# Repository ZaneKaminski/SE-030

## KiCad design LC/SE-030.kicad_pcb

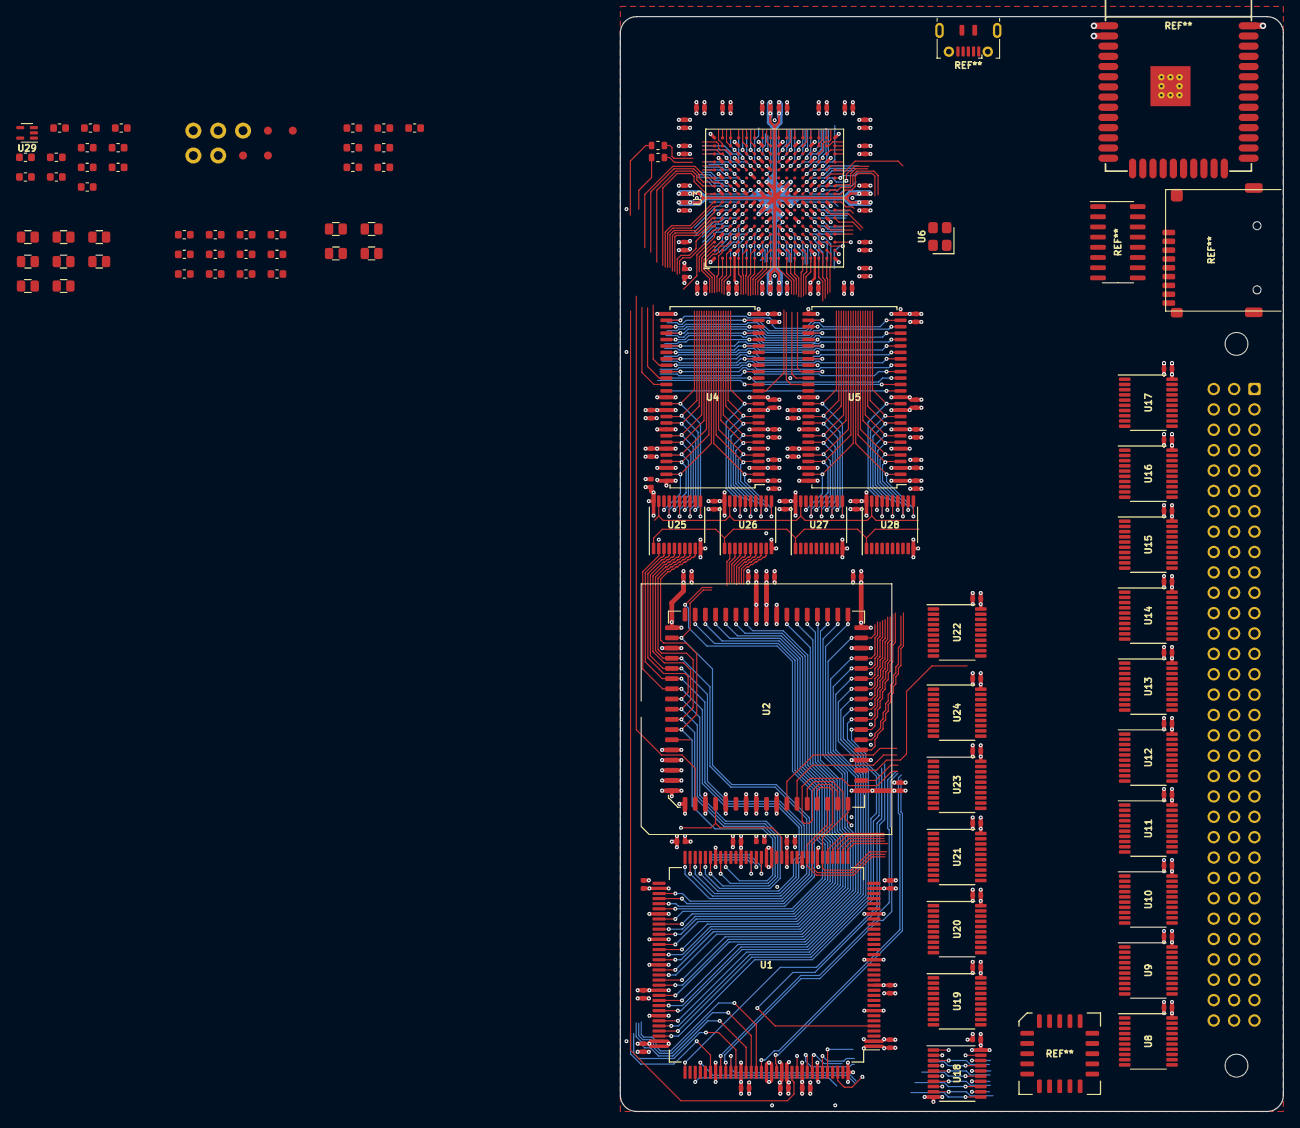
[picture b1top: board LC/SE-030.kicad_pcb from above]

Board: 4 copper layers, 82.7 x 136.5 mm, 80 parts (0 on the bottom side), 175 nets.

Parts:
C4, C5, C6, C7, C8, C9, C10, C11, C12, C13, C14, C15: 10u; C_0805
C16, C17, C18, C19, C20, C21, C22, C23, C24, C25, C26, C27, C28, C29, C30, C31, C32, C33, C34, C35, C36, C37, C38, C39, C40, C41, C42, C43, C44, C45, C46: 2u2; C_0603
FID1, FID2, FID3, FID4: Fiducial
H1, H2, H3, H4, H5: PasteHole_1.1mm_PTH
U1: MC68030FE; PQFP-132_24x24mm_P0.635mm_MC68030
U2: MC68882FN; PLCC-68_SMDSocket
U3: XC6SLX9-FTG256; BGA-256_17.0x17.0mm_Layout16x16_P1.0mm_Ball0.5mm_Pad0.4mm_N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
U4, U5: W9825G6KH-6; TSOP-II-54_22.2x10.16mm_P0.8mm
U6: 50M; Crystal_SMD_3225-4Pin_3.2x2.5mm
U8, U9, U10, U11, U12, U22: 74AHCT573PW; TSSOP-20_4.4x6.5mm_P0.65mm
U13, U23, U24: 74LVC244APW; TSSOP-20_4.4x6.5mm_P0.65mm
U14, U15, U16, U17, U25, U26, U27, U28: 74AHC245APW; TSSOP-20_4.4x6.5mm_P0.65mm
U18, U19, U20, U21: 74LVC244; TSSOP-20_4.4x6.5mm_P0.65mm
U29: 74LVC1G125GW; SOT-353

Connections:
+1V2: U3.G7, U3.G9, U3.H8, U3.H10, U3.J7, U3.J9, U3.K8, U3.K10
+3V3: C16.1, C17.1, C18.1, C19.1, C20.1, C21.1, C22.1, C23.1, C24.1, C25.1, C26.1, C27.1, C28.1, C29.1, C30.1, C31.1, C32.1, C33.1, C34.1, C35.1, C36.1, C37.1, C38.1, C39.1, C40.1, C41.1, C42.1, C43.1, C44.1, C45.1, C46.1, U3.B4, U3.B9, U3.B13, U3.D2, U3.D7, U3.D10, U3.D15, U3.E5, U3.F8, U3.F11, U3.G4, U3.G10, U3.G13, U3.H6, U3.J2, U3.J10, U3.J15, U3.K4, U3.K13, U3.L6, U3.L9, U3.N2, U3.N7, U3.N10, U3.N15, U3.R4, U3.R8, U3.R13, U4.1, U4.3, U4.9, U4.14, U4.27, U4.43, U4.49, U5.1, U5.3, U5.9, U5.14, U5.27, U5.43, U5.49, U13.20, U14.20, U15.20, U16.20, U17.20, U18.20, U19.20, U20.20, U21.20, U22.11, U22.20, U23.20, U24.20, U25.20, U26.20, U27.20, U28.20, U29.5
+5V: C4.1, C5.1, C12.1, C13.1, C14.1, C15.1, U1.4, U1.8, U1.17, U1.18, U1.20, U1.30, U1.49, U1.63, U1.65, U1.71, U1.72, U1.85, U1.105, U1.115, U1.116, U1.128, U2.10, U2.16, U2.17, U2.18, U2.26, U2.27, U2.43, U2.52, U2.53, U2.61, U8.11, U8.20, U9.20, U10.20, U11.20, U12.6, U12.20
+12V: C8.1, C9.1
-5V: C6.1, C7.1
-12V: C10.1, C11.1
/CPUBuf/A~OE~: U18.1, U18.19, U19.1, U19.19, U20.1, U20.19, U21.1, U21.19, U24.1, U24.19
/CPUBuf/CPU_D0: U1.75, U2.3, U25.9
/CPUBuf/CPU_D1: U1.76, U2.2, U25.8
/CPUBuf/CPU_D2: U1.78, U2.1, U25.6
/CPUBuf/CPU_D3: U1.79, U2.68, U25.4
/CPUBuf/CPU_D4: U1.80, U2.67, U25.2
/CPUBuf/CPU_D5: U1.81, U2.66, U25.3
/CPUBuf/CPU_D6: U1.82, U2.65, U25.5
/CPUBuf/CPU_D7: U1.83, U2.64, U25.7
/CPUBuf/CPU_D8: U1.86, U2.62, U26.3
/CPUBuf/CPU_D9: U1.87, U2.60, U26.2
/CPUBuf/CPU_D10: U1.88, U2.59, U26.4
/CPUBuf/CPU_D11: U1.89, U2.58, U26.5
/CPUBuf/CPU_D12: U1.91, U2.57, U26.6
/CPUBuf/CPU_D13: U1.92, U2.56, U26.7
/CPUBuf/CPU_D14: U1.93, U2.55, U26.8
/CPUBuf/CPU_D15: U1.94, U2.54, U26.9
/CPUBuf/CPU_D16: U1.96, U2.50, U27.2
/CPUBuf/CPU_D17: U1.97, U2.49, U27.3
/CPUBuf/CPU_D18: U1.98, U2.48, U27.4
/CPUBuf/CPU_D19: U1.99, U2.47, U27.5
/CPUBuf/CPU_D20: U1.101, U2.46, U27.6
/CPUBuf/CPU_D21: U1.102, U2.45, U27.7
/CPUBuf/CPU_D22: U1.103, U2.44, U27.9
/CPUBuf/CPU_D23: U1.104, U2.42, U27.8
/CPUBuf/CPU_D24: U1.106, U2.40, U28.2
/CPUBuf/CPU_D25: U1.107, U2.39, U28.3
/CPUBuf/CPU_D26: U1.108, U2.38, U28.4
/CPUBuf/CPU_D27: U1.109, U2.37, U28.5
/CPUBuf/CPU_D28: U1.111, U2.36, U28.6
/CPUBuf/CPU_D29: U1.112, U2.35, U28.7
/CPUBuf/CPU_D30: U1.113, U2.34, U28.8
/CPUBuf/CPU_D31: U1.114, U2.33, U28.9
/CPUBuf/CPU_FC0: U1.12, U24.17
/CPUBuf/CPU_FC1: U1.10, U24.8
/CPUBuf/CPU_FC2: U1.9, U24.6
/CPUBuf/CPU_R~W~: U1.117, U2.28, U24.4
/CPUBuf/CPU_SIZ0: U1.120, U23.15
/CPUBuf/CPU_SIZ1: U1.119, U23.13
/CPUBuf/CPU_~AS~: U1.125, U2.21, U23.2
/CPUBuf/CPU_~CBREQ~: U1.126, U23.4
/CPUBuf/CPU_~CIOUT~: U1.15, U23.17
/CPUBuf/CPU_~DSACK~0: U1.3, U2.31, U22.18
/CPUBuf/CPU_~DSACK~1: U1.132, U2.32, U22.19
/CPUBuf/CPU_~DS~: U1.124, U2.20, U23.6
/CPUBuf/CPU_~ECS~: U1.118, U23.8
/CPUBuf/CPU_~RMC~: U1.13, U24.2
/CPUBuf/FSB_A4: U12.5, U18.3
/CPUBuf/FSB_A5: U12.4, U18.5
/CPUBuf/FSB_A6: U12.3, U18.7
/CPUBuf/FSB_A7: U12.2, U18.9
/CPUBuf/FSB_A8: U11.9, U19.12
/CPUBuf/FSB_A9: U11.8, U19.14
/CPUBuf/FSB_A10: U11.7, U19.16
/CPUBuf/FSB_A11: U11.6, U19.18
/CPUBuf/FSB_A12: U11.5, U19.3
/CPUBuf/FSB_A13: U11.4, U19.5
/CPUBuf/FSB_A14: U11.3, U19.7
/CPUBuf/FSB_A15: U11.2, U19.9
/CPUBuf/FSB_A16: U10.9, U20.12
/CPUBuf/FSB_A17: U10.8, U20.14
/CPUBuf/FSB_A18: U10.7, U20.16
/CPUBuf/FSB_A19: U10.6, U20.18
/CPUBuf/FSB_A20: U10.5, U20.3
/CPUBuf/FSB_A21: U10.4, U20.5
/CPUBuf/FSB_A22: U10.3, U20.7
/CPUBuf/FSB_A23: U10.2, U20.9
/CPUBuf/FSB_A24: U9.9, U21.12
/CPUBuf/FSB_A25: U9.8, U21.14
/CPUBuf/FSB_A26: U9.7, U21.16
/CPUBuf/FSB_A27: U9.6, U21.18
/CPUBuf/FSB_A30: U9.5, U21.7
/CPUBuf/FSB_A31: U9.4, U21.9
/CPUBuf/FSB_FC0: U12.9, U24.3
/CPUBuf/FSB_FC1: U12.8, U24.18
/CPUBuf/FSB_FC2: U12.7, U24.16
/CPUBuf/FSB_R~W~: U9.3, U24.14
/Control/CPU_DDIR: U25.1, U26.1, U27.1, U28.1
/Control/CPU_D~OE~: U25.19, U26.19, U27.19, U28.19
/Control/RAM_~CAS~: U4.17, U5.17
/Control/RAM_~CS~: U4.19, U5.19
/Control/RAM_~RAS~: U4.18, U5.18
/Control/RAM_~WE~: U4.16, U5.16
/MC68k/A0: U1.21, U18.2
/MC68k/A1: U1.22, U2.25, U18.4
/MC68k/A2: U1.59, U2.24, U18.6
/MC68k/A3: U1.58, U2.23, U18.8
/MC68k/A4: U1.56, U2.22, U18.17
/MC68k/A5: U1.55, U18.15
/MC68k/A6: U1.54, U18.13
/MC68k/A7: U1.53, U18.11
/MC68k/A8: U1.52, U19.2
/MC68k/A9: U1.51, U19.4
/MC68k/A10: U1.48, U19.6
/MC68k/A11: U1.47, U19.8
/MC68k/A12: U1.46, U19.17
/MC68k/A13: U1.45, U19.15
/MC68k/A14: U1.43, U19.13
/MC68k/A15: U1.42, U19.11
/MC68k/A16: U1.41, U20.2
/MC68k/A17: U1.40, U20.4
/MC68k/A18: U1.39, U20.6
/MC68k/A19: U1.38, U20.8
/MC68k/A20: U1.37, U20.17
/MC68k/A21: U1.36, U20.15
/MC68k/A22: U1.34, U20.13
/MC68k/A23: U1.33, U20.11
/MC68k/A24: U1.32, U21.2
/MC68k/A25: U1.31, U21.4
/MC68k/A26: U1.29, U21.6
/MC68k/A27: U1.28, U21.8
/MC68k/A28: U1.27, U21.17
/MC68k/A29: U1.26, U21.15
/MC68k/A30: U1.24, U21.13
/MC68k/A31: U1.23, U21.11
/PDSBuf/ADoutLE: U9.11, U10.11, U11.11, U12.11
/PDSBuf/A~OE~: U8.1, U9.1, U10.1, U11.1, U12.1
/PDSBuf/DDIR: U14.1, U15.1, U16.1, U17.1
/PDSBuf/D~OE~: U14.19, U15.19, U16.19, U17.19
/PDSBuf/IOB_~RESET~: U1.64, U2.13, U13.2
/RAM/BA0: U4.20, U5.20
/RAM/BA1: U4.21, U5.21
/RAM/CKE: U4.37, U5.37
/RAM/D0: U4.2, U25.11
/RAM/D1: U4.4, U25.12
/RAM/D2: U4.5, U25.14
/RAM/D3: U4.7, U25.16
/RAM/D4: U4.8, U25.18
/RAM/D5: U4.10, U25.17
/RAM/D6: U4.11, U25.15
/RAM/D7: U4.13, U25.13
/RAM/D8: U4.42, U26.17
/RAM/D9: U4.44, U26.18
/RAM/D10: U4.45, U26.16
/RAM/D11: U4.47, U26.15
/RAM/D12: U4.48, U26.14
/RAM/D13: U4.50, U26.13
/RAM/D14: U4.51, U26.12
/RAM/D15: U4.53, U26.11
/RAM/D16: U5.2, U27.18
/RAM/D17: U5.4, U27.17
/RAM/D18: U5.5, U27.16
/RAM/D19: U5.7, U27.15
/RAM/D20: U5.8, U27.14
/RAM/D21: U5.10, U27.13
/RAM/D22: U5.11, U27.11
/RAM/D23: U5.13, U27.12
/RAM/D24: U5.42, U28.18
/RAM/D25: U5.44, U28.17
/RAM/D26: U5.45, U28.16
/RAM/D27: U5.47, U28.15
/RAM/D28: U5.48, U28.14
/RAM/D29: U5.50, U28.13
/RAM/D30: U5.51, U28.12
/RAM/D31: U5.53, U28.11
/RAM/RA0: U4.23, U5.23
/RAM/RA1: U4.24, U5.24
/RAM/RA2: U4.25, U5.25
/RAM/RA3: U4.26, U5.26
/RAM/RA4: U4.29, U5.29
/RAM/RA5: U4.30, U5.30
/RAM/RA6: U4.31, U5.31
/RAM/RA7: U4.32, U5.32
/RAM/RA8: U4.33, U5.33
/RAM/RA9: U4.34, U5.34
/RAM/RA10: U4.22, U5.22
/RAM/RA11: U4.35, U5.35
/RAM/RA12: U4.36, U5.36
GND: C4.2, C5.2, C6.2, C7.2, C8.2, C9.2, C10.2, C11.2, C12.2, C13.2, C14.2, C15.2, C16.2, C17.2, C18.2, C19.2, C20.2, C21.2, C22.2, C23.2, C24.2, C25.2, C26.2, C27.2, C28.2, C29.2, C30.2, C31.2, C32.2, C33.2, C34.2, C35.2, C36.2, C37.2, C38.2, C39.2, C40.2, C41.2, C42.2, C43.2, C44.2, C45.2, C46.2, H1.1, H2.1, H3.1, H4.1, H5.1, U1.1, U1.2, U1.5, U1.7, U1.11, U1.19, U1.25, U1.35, U1.44, U1.57, U1.60, U1.66, U1.67, U1.77, U1.90, U1.95, U1.100, U1.110, U1.123, U2.5, U2.6, U2.7, U2.8, U2.9, U2.12, U2.14, U2.19, U2.30, U2.41, U2.51, U2.63, U3.A1, U3.A16, U3.B7, U3.B11, U3.D4, U3.D13, U3.E9, U3.G2, U3.G8, U3.G15, U3.H7, U3.H9, U3.H12, U3.J5, U3.J8, U3.K7, U3.K9, U3.L2, U3.L15, U3.M8, U3.N13, U3.P3, U3.R6, U3.R10, U3.T1, U3.T16, U4.6, U4.12, U4.28, U4.41, U4.46, U4.52, U4.54, U5.6, U5.12, U5.28, U5.41, U5.46, U5.52, U5.54, U8.10, U9.2, U9.10, U10.10, U11.10, U12.10, U13.1, U13.10, U13.11, U13.13, U13.19, U14.10, U15.10, U16.10, U17.10, U18.10, U19.10, U20.10, U21.10, U22.10, U23.1, U23.10, U23.11, U23.19, U24.10, U24.11, U24.13, U24.15, U25.10, U26.10, U27.10, U28.10, U29.2, U29.3

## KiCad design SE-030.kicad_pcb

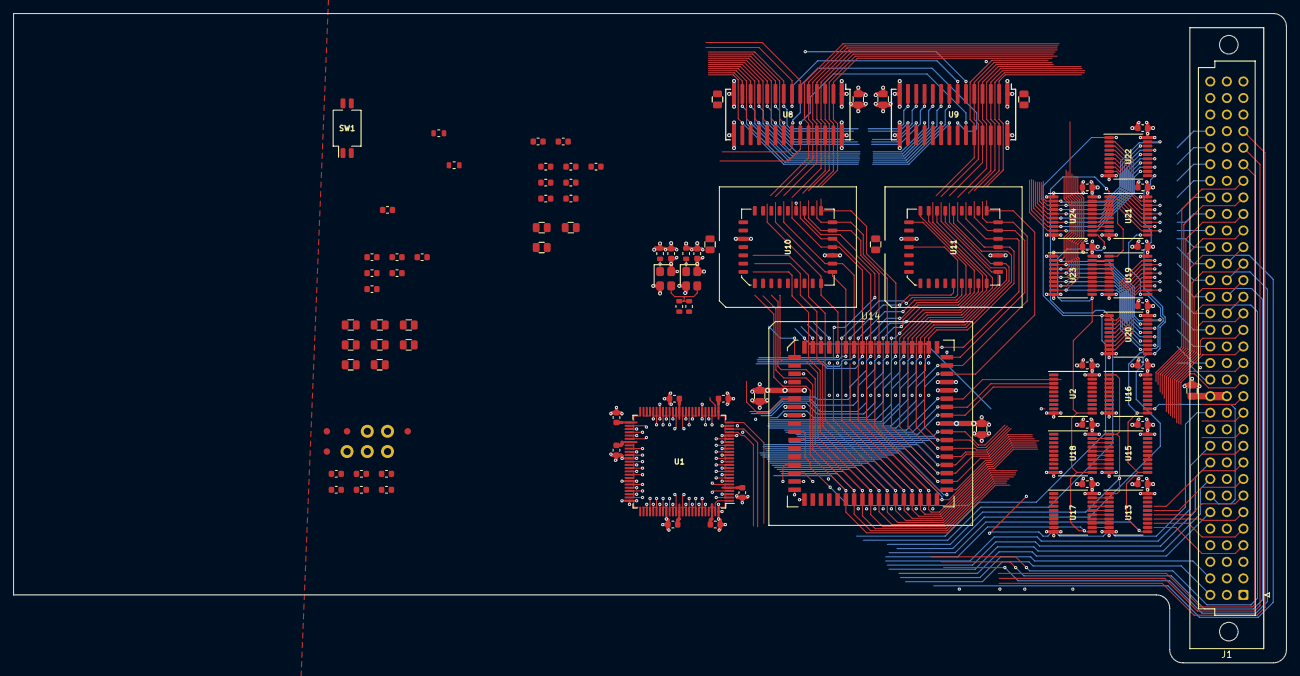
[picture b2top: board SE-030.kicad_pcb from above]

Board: 4 copper layers, 195.2 x 99.6 mm, 100 parts (0 on the bottom side), 178 nets.

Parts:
C1, C1#2, C1#3, C1#4, C1#5, C1#6, C1#7, C1#8, C1#9, C2, C3, C4, C18, C19, C20, C21, C22, C23, C24, C25: 10u; C_0805
C5, C6, C7, C10, C11, C12, C13, C14, C14#2, C14#3, C14#4, C14#5, C14#6, C14#7, C14#8, C14#9, C14#10, C14#11, C14#12, C14#13, C15, C16, C17, C26, C27, C28, C29, C30, C31, C32, C33, C34, C35, C36, C37, C38, C39, C40, C41, C41#2, C42, C43, C44: 2u2; C_0603
FID1, FID2, FID3, FID4: Fiducial
H1, H2, H3, H4, H5: PasteHole_1.1mm_PTH
J1: MacSEPDS; DIN41612_R_3x32_Male_Vertical_THT
R1, R2, R6, R12: 22; R_0603
R10, R11: 10k; R_0603
SW1: OSCSEL; SW_DIP_SPSTx02_Slide_DSHP02TS_P1.27mm
U1: XC95144XL-TQ100; TQFP-100_14x14mm_P0.5mm
U2, U13, U15, U16, U17, U18, U19, U20, U21, U22, U23, U24: 74AHCT573; TSSOP-20_4.4x6.5mm_P0.65mm
U4: 20M; Crystal_SMD_3225-4Pin_3.2x2.5mm
U5: 25M; Crystal_SMD_3225-4Pin_3.2x2.5mm
U8, U9: KM48C2100; SOJ-28_300mil
U10, U11: 39SF040; PLCC-32_SMDSocket
U14: MC68HC000FN20; PLCC-68_SMD-Socket

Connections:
+3V3: C5.1, C6.1, C7.1, C26.1, C27.1, C28.1, C29.1, C30.1, C31.1, C32.1, C33.1, C34.1, C35.1, C36.1, C37.1, C38.1, C39.1, C40.1, C41.1, C41#2.1, C42.1, C43.1, C44.1, R12.1, U1.5, U1.26, U1.38, U1.51, U1.57, U1.88, U1.98, U4.4, U5.4, U10.32, U11.32
+5V: C1.1, C1#2.1, C1#3.1, C1#4.1, C1#5.1, C1#6.1, C1#7.1, C1#8.1, C1#9.1, C2.1, C3.1, C4.1, C10.1, C11.1, C12.1, C13.1, C14.1, C14#2.1, C14#3.1, C14#4.1, C14#5.1, C14#6.1, C14#7.1, C14#8.1, C14#9.1, C14#10.1, C14#11.1, C14#12.1, C14#13.1, C15.1, C16.1, C17.1, C18.1, C19.1, J1.B13, J1.B14, J1.B15, J1.B16, J1.B17, J1.C4, J1.C13, U2.20, U13.20, U14.12, U14.13, U14.14, U14.52, U15.20, U16.20, U17.20, U18.20, U19.20, U20.20, U21.20, U22.20, U23.20, U24.20
+12V: C22.1, C23.1
-5V: C20.1, C21.1
-12V: C24.1, C25.1
/Buf/ADoutLE0: U1.4, U13.11, U15.11, U16.11, U19.11, U21.11
/Buf/ADoutLE1: U1.3, U2.11, U17.11, U18.11, U23.11, U24.11
/Buf/AccD0: U8.2, U10.13, U14.5, U20.12, U23.9
/Buf/AccD1: U8.3, U10.14, U14.4, U20.13, U23.8
/Buf/AccD2: U8.4, U10.15, U14.3, U20.14, U23.7
/Buf/AccD3: U8.5, U10.17, U14.2, U20.15, U23.6
/Buf/AccD4: U8.24, U10.18, U14.1, U20.16, U23.5
/Buf/AccD5: U8.25, U10.19, U14.68, U20.17, U23.4
/Buf/AccD6: U8.26, U10.20, U14.67, U20.18, U23.3
/Buf/AccD7: U8.27, U10.21, U14.66, U20.19, U23.2
/Buf/AccD8: U9.2, U11.13, U14.65, U22.12, U24.9
/Buf/AccD9: U9.3, U11.14, U14.64, U22.13, U24.8
/Buf/AccD10: U9.4, U11.15, U14.63, U22.14, U24.7
/Buf/AccD11: U9.5, U11.17, U14.62, U22.15, U24.6
/Buf/AccD12: U9.24, U11.18, U14.61, U22.16, U24.5
/Buf/AccD13: U9.25, U11.19, U14.60, U22.17, U24.4
/Buf/AccD14: U9.26, U11.20, U14.59, U22.18, U24.3
/Buf/AccD15: U9.27, U11.21, U14.58, U22.19, U24.2
/Buf/Aout~OE~: U1.2, U13.1, U15.1, U16.1
/Buf/DinLE: U1.8, U20.11, U22.11
/Buf/Din~OE~: U1.7, U20.1, U22.1
/Buf/Dout~OE~: U1.6, U19.1, U21.1
/Buf/Mac~R~W: J1.C7, U16.12
/Control/A1: U1.77, U10.12, U11.12, U14.32, U17.9
/Control/A2: U1.76, U10.11, U11.11, U14.33, U17.8
/Control/A3: U1.74, U10.10, U11.10, U14.34, U17.7
/Control/A4: U1.49, U10.9, U11.9, U14.35, U17.6
/Control/A5: U1.46, U10.8, U11.8, U14.36, U17.5
/Control/A6: U1.43, U10.7, U11.7, U14.37, U17.4
/Control/A7: U1.42, U10.6, U11.6, U14.38, U17.3
/Control/A8: U1.41, U10.5, U11.5, U14.39, U17.2
/Control/A9: U1.40, U10.27, U11.27, U14.40, U18.9
/Control/A10: U1.39, U10.26, U11.26, U14.41, U18.8
/Control/A11: U1.37, U10.23, U11.23, U14.42, U18.7
/Control/A12: U1.36, U10.25, U11.25, U14.43, U18.6
/Control/A13: U1.35, U10.4, U11.4, U14.44, U18.5
/Control/A14: U1.20, U10.28, U11.28, U14.45, U18.4
/Control/A15: U1.19, U10.29, U11.29, U14.46, U18.3
/Control/A16: U1.18, U10.3, U11.3, U14.47, U18.2
/Control/A17: U1.17, U2.8, U10.2, U11.2, U14.48
/Control/A18: U1.16, U2.7, U10.30, U11.30, U14.49
/Control/A19: U1.15, U2.6, U10.1, U11.1, U14.50
/Control/A20: U1.14, U2.5, U14.51
/Control/A21: U1.13, U2.4, U14.53
/Control/A22: U1.12, U2.3, U14.54
/Control/A23: U1.11, U2.2, U14.55
/Control/AccR~W~: U1.78, U2.9, U14.9
/Control/Acc~AS~: U1.70, U14.6
/Control/Acc~BERR~: U1.72, U14.24
/Control/Acc~DTACK: U1.71, U14.10
/Control/Acc~LDS~: U1.68, U14.8
/Control/Acc~UDS~: U1.67, U14.7
/Control/Acc~VPA~: U1.73, U14.23
/Control/C8M: J1.A28, U1.27
/Control/C16M: J1.A29, U1.23
/Control/FCLK: R2.2, U1.22
/Control/L~WE~: U1.65, U8.6, U10.31
/Control/Mac~AS~: J1.C10, U1.87
/Control/Mac~BERR~: J1.B21, U1.94
/Control/Mac~DTACK~: J1.C6, U1.92
/Control/Mac~LDS~: J1.C8, U1.90
/Control/Mac~UDS~: J1.C9, U1.91
/Control/Mac~VMA~: J1.C2, U1.89
/Control/Mac~VPA~: J1.C1, U1.93
/Control/RA0: U1.81, U8.10, U9.10
/Control/RA1: U1.82, U8.11, U9.11
/Control/RA2: U1.85, U8.12, U9.12
/Control/RA3: U1.86, U8.13, U9.13
/Control/RA4: U1.50, U8.16, U9.16
/Control/RA5: U1.52, U8.17, U9.17
/Control/RA6: U1.53, U8.18, U9.18
/Control/RA7: U1.54, U8.19, U9.19
/Control/RA8: U1.55, U8.20, U9.20
/Control/RA9: U1.56, U8.21, U9.21
/Control/RA10: U1.58, U8.9, U9.9
/Control/RA11: U1.59, U8.8, U9.8
/Control/ROM~CS~: U1.63, U10.22, U11.22
/Control/U~WE~: U1.66, U9.6, U11.31
/Control/~CAS~: U1.61, U8.23, U9.23
/Control/~OE~: U1.64, U8.22, U9.22, U10.24, U11.24
/Control/~RAS~: U1.60, U8.7, U9.7
/Control/~RESET~r: U1.1, U1.99
/MC68k/CLK: R1.2, U14.15
/MC68k/~HALT~: J1.C12, U1.10, U14.19, U14.20
/MC68k/~IPL~0: J1.B18, U14.27
/MC68k/~IPL~1: J1.B19, U14.26
/MC68k/~IPL~2: J1.B20, U14.25
/PDS/A1: J1.A4, U13.12
/PDS/A2: J1.A5, U13.13
/PDS/A3: J1.A6, U13.14
/PDS/A4: J1.A7, U13.15
/PDS/A5: J1.A8, U13.16
/PDS/A6: J1.A9, U13.17
/PDS/A7: J1.A10, U13.18
/PDS/A8: J1.A11, U13.19
/PDS/A9: J1.A12, U15.12
/PDS/A10: J1.A13, U15.13
/PDS/A11: J1.A14, U15.14
/PDS/A12: J1.A15, U15.15
/PDS/A13: J1.A16, U15.16
/PDS/A14: J1.A17, U15.17
/PDS/A15: J1.A18, U15.18
/PDS/A16: J1.A19, U15.19
/PDS/A17: J1.A20, U16.13
/PDS/A18: J1.A21, U16.14
/PDS/A19: J1.A22, U16.15
/PDS/A20: J1.A23, U16.16
/PDS/A21: J1.A24, U16.17
/PDS/A22: J1.A25, U16.18
/PDS/A23: J1.A26, U16.19
/PDS/D0: J1.C14, U19.12, U20.9
/PDS/D1: J1.C15, U19.13, U20.8
/PDS/D2: J1.C16, U19.14, U20.7
/PDS/D3: J1.C17, U19.15, U20.6
/PDS/D4: J1.C18, U19.16, U20.5
/PDS/D5: J1.C19, U19.17, U20.4
/PDS/D6: J1.C20, U19.18, U20.3
/PDS/D7: J1.C21, U19.19, U20.2
/PDS/D8: J1.C22, U21.12, U22.9
/PDS/D9: J1.C23, U21.13, U22.8
/PDS/D10: J1.C24, U21.14, U22.7
/PDS/D11: J1.C25, U21.15, U22.6
/PDS/D12: J1.C26, U21.16, U22.5
/PDS/D13: J1.C27, U21.17, U22.4
/PDS/D14: J1.C28, U21.18, U22.3
/PDS/D15: J1.C29, U21.19, U22.2
/PDS/E: J1.A27, U1.95
GND: C1.2, C1#2.2, C1#3.2, C1#4.2, C1#5.2, C1#6.2, C1#7.2, C1#8.2, C1#9.2, C2.2, C3.2, C4.2, C5.2, C6.2, C7.2, C10.2, C11.2, C12.2, C13.2, C14.2, C14#2.2, C14#3.2, C14#4.2, C14#5.2, C14#6.2, C14#7.2, C14#8.2, C14#9.2, C14#10.2, C14#11.2, C14#12.2, C14#13.2, C15.2, C16.2, C17.2, C18.2, C19.2, C20.2, C21.2, C22.2, C23.2, C24.2, C25.2, C26.2, C27.2, C28.2, C29.2, C30.2, C31.2, C32.2, C33.2, C34.2, C35.2, C36.2, C37.2, C38.2, C39.2, C40.2, C41.2, C41#2.2, C42.2, C43.2, C44.2, H1.1, H2.1, H3.1, H4.1, H5.1, J1.A30, J1.B1, J1.B2, J1.B3, J1.B4, J1.B5, J1.B6, J1.B7, J1.B8, J1.B9, J1.B29, J1.C3, J1.C30, R10.1, R11.1, U1.21, U1.31, U1.44, U1.62, U1.69, U1.75, U1.84, U1.100, U2.1, U2.10, U4.2, U5.2, U8.15, U8.28, U9.15, U9.28, U10.16, U11.16, U13.10, U14.16, U14.17, U14.56, U14.57, U15.10, U16.10, U17.1, U17.10, U18.1, U18.10, U19.10, U20.10, U21.10, U22.10, U23.1, U23.10, U24.1, U24.10
unnamed: R1.1, R2.1, U4.3, U5.3
unnamed: R10.2, SW1.2, U5.1
unnamed: R11.2, SW1.1, U4.1
unnamed: R12.2, SW1.3, SW1.4
unnamed: U13.2, U17.19
unnamed: U13.3, U17.18
unnamed: U13.4, U17.17
unnamed: U13.5, U17.16
unnamed: U13.6, U17.15
unnamed: U13.7, U17.14
unnamed: U13.8, U17.13
unnamed: U13.9, U17.12
unnamed: U15.2, U18.19
unnamed: U15.3, U18.18
unnamed: U15.4, U18.17
unnamed: U15.5, U18.16
unnamed: U15.6, U18.15
unnamed: U15.7, U18.14
unnamed: U15.8, U18.13
unnamed: U15.9, U18.12
unnamed: U2.19, U16.2
unnamed: U2.18, U16.3
unnamed: U2.17, U16.4
unnamed: U2.16, U16.5
unnamed: U2.15, U16.6
unnamed: U2.14, U16.7
unnamed: U2.13, U16.8
unnamed: U2.12, U16.9
unnamed: U19.2, U23.19
unnamed: U19.3, U23.18
unnamed: U19.4, U23.17
unnamed: U19.5, U23.16
unnamed: U19.6, U23.15
unnamed: U19.7, U23.14
unnamed: U19.8, U23.13
unnamed: U19.9, U23.12
unnamed: U21.2, U24.19
unnamed: U21.3, U24.18
unnamed: U21.4, U24.17
unnamed: U21.5, U24.16
unnamed: U21.6, U24.15
unnamed: U21.7, U24.14
unnamed: U21.8, U24.13
unnamed: U21.9, U24.12
VDD: U8.1, U8.14, U9.1, U9.14

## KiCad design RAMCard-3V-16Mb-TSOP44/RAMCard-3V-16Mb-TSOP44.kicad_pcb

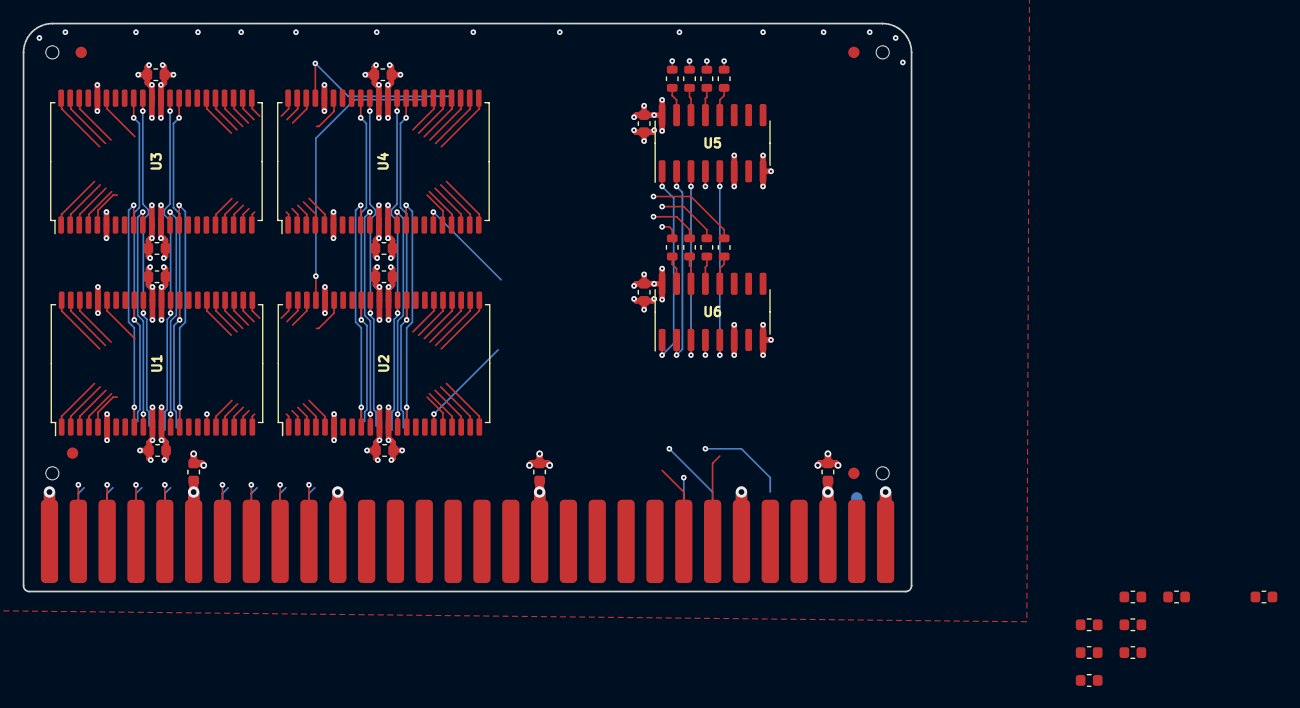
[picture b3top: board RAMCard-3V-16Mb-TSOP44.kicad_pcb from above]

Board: 4 copper layers, 78.2 x 50.0 mm, 44 parts (0 on the bottom side), 60 nets.

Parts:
C1, C2, C3, C4, C5, C6, C7, C8, C9, C9#2, C9#3, C12, C12#2, C13, C14, C15, C17, C18, C20, C21, C22: 2u2; C_0603
FID1, FID2, FID3, FID4: Fiducial
H1, H2, H3, H4: PasteHole_1.152mm_NPTH
J1: RAM; AppleIIeAux_Edge
R1, R2, R3, R4, R5, R6, R7, R8: 47; R_0603
U1, U2, U3, U4: SRAM-1Mx8-TSOP2-44; TSOP-II-44_400mil_P0.8mm
U5, U6: 74LVC138D; SOIC-16_3.9mm

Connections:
+5V: C1.1, C2.1, C3.1, C4.1, C5.1, C6.1, C7.1, C8.1, C9.1, C9#2.1, C9#3.1, C12.1, C12#2.1, C13.1, C14.1, C15.1, C17.1, C18.1, C20.1, C21.1, C22.1, J1.6, J1.18, J1.28, J1.33, J1.43, J1.55, U1.11, U1.33, U1.40, U2.11, U2.33, U2.40, U3.11, U3.33, U3.40, U4.11, U4.33, U4.40, U5.6, U5.16, U6.6, U6.16
/A1: J1.12, U1.5, U2.18, U3.5, U4.18
/A2: J1.49, U1.4, U2.19, U3.4, U4.19
/A3: J1.13, U1.3, U2.20, U3.3, U4.20
/A4: J1.48, U1.2, U2.21, U3.2, U4.21
/A5: J1.14, U1.1, U2.22, U3.1, U4.22
/A6: J1.47, U1.44, U2.23, U3.44, U4.23
/A7: J1.15, U1.43, U2.24, U3.43, U4.24
/A8: J1.46, U1.42, U2.25, U3.42, U4.25
/A9: J1.16, U1.39, U2.26, U3.39, U4.26
/A10: J1.45, U1.28, U2.27, U3.28, U4.27
/A11: J1.17, U1.27, U2.28, U3.27, U4.28
/A12: J1.44, U1.26, U2.39, U3.26, U4.39
/A13: J1.19, U1.25, U2.42, U3.25, U4.42
/A14: J1.42, U1.24, U2.43, U3.24, U4.43
/A15: J1.20, U1.23, U2.44, U3.23, U4.44
/A16: J1.41, U1.22, U2.1, U3.22, U4.1
/A17: J1.21, U1.21, U2.2, U3.21, U4.2
/A18: J1.40, U1.20, U2.3, U3.20, U4.3
/A19: J1.22, U1.19, U2.4, U3.19, U4.4
/A20: J1.39, U1.18, U2.5, U3.18, U4.5
/A21: J1.23, U5.1, U6.1
/A22: J1.38, U5.3, U6.3
/A23: J1.24, U5.5, U6.5
/D0: J1.2, U1.9, U3.9
/D1: J1.59, U1.10, U3.10
/D2: J1.3, U1.13, U3.13
/D3: J1.58, U1.14, U3.14
/D4: J1.4, U1.31, U3.31
/D5: J1.57, U1.32, U3.32
/D6: J1.5, U1.35, U3.35
/D7: J1.56, U1.36, U3.36
/D8: J1.7, U2.9, U4.9
/D9: J1.54, U2.10, U4.10
/D10: J1.8, U2.13, U4.13
/D11: J1.53, U2.14, U4.14
/D12: J1.9, U2.31, U4.31
/D13: J1.52, U2.32, U4.32
/D14: J1.10, U2.35, U4.35
/D15: J1.51, U2.36, U4.36
/L~OE~0: R5.1, U3.41
/L~OE~1: R7.1, U1.41
/L~WE~0: R1.1, U3.17
/L~WE~1: R3.1, U1.17
/R~W~: J1.37, U5.2, U6.2
/U~OE~0: R6.1, U4.41
/U~OE~1: R8.1, U2.41
/U~WE~0: R2.1, U4.17
/U~WE~1: R4.1, U2.17
/~LDS~: J1.35, U5.4
/~UDS~: J1.34, U6.4
GND: C1.2, C2.2, C3.2, C4.2, C5.2, C6.2, C7.2, C8.2, C9.2, C9#2.2, C9#3.2, C12.2, C12#2.2, C13.2, C14.2, C15.2, C17.2, C18.2, C20.2, C21.2, C22.2, J1.1, J1.11, J1.25, J1.30, J1.31, J1.32, J1.36, J1.50, J1.60, U1.6, U1.12, U1.34, U2.6, U2.12, U2.34, U3.6, U3.12, U3.34, U4.6, U4.12, U4.34, U5.8, U6.8
unnamed: R1.2, U5.15
unnamed: R2.2, U6.15
unnamed: R3.2, U5.14
unnamed: R4.2, U6.14
unnamed: R5.2, U5.13
unnamed: R6.2, U6.13
unnamed: R7.2, U5.12
unnamed: R8.2, U6.12

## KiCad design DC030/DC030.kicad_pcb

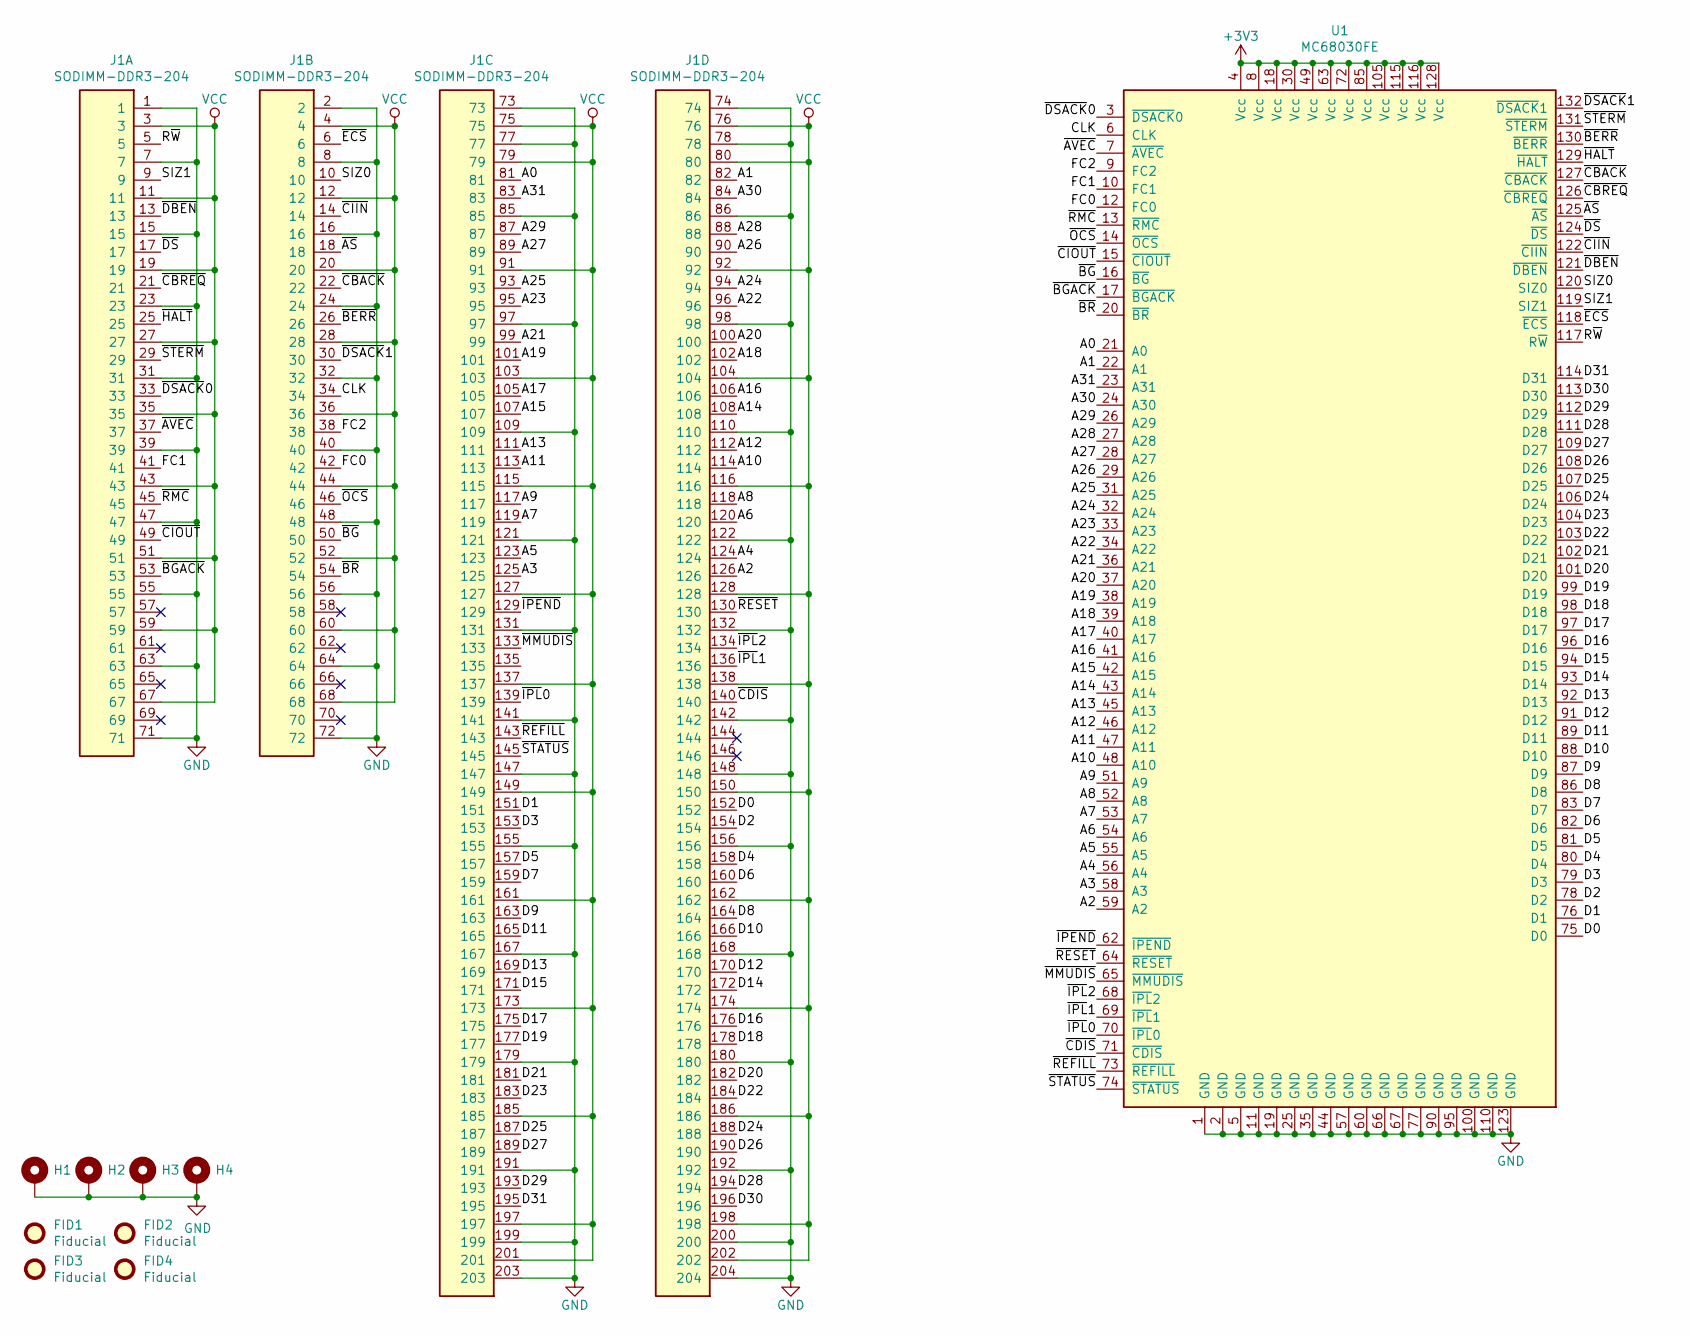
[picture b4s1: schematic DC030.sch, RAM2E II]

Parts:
FID1, FID2, FID3, FID4: Fiducial
H1, H2, H3, H4: PasteHole_1.1mm_PTH
J1: SODIMM-DDR3-204; SODIMM_DDR3_Edge
U1: MC68030FE; Motorola_CQFP-132

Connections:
+3V3: U1.4 (Vcc), U1.8 (Vcc), U1.18 (Vcc), U1.30 (Vcc), U1.49 (Vcc), U1.63 (Vcc), U1.72 (Vcc), U1.85 (Vcc), U1.105 (Vcc), U1.115 (Vcc), U1.116 (Vcc), U1.128 (Vcc)
/A0: J1.81, U1.21 (A0)
/A1: J1.82, U1.22 (A1)
/A2: J1.126, U1.59 (A2)
/A3: J1.125, U1.58 (A3)
/A4: J1.124, U1.56 (A4)
/A5: J1.123, U1.55 (A5)
/A6: J1.120, U1.54 (A6)
/A7: J1.119, U1.53 (A7)
/A8: J1.118, U1.52 (A8)
/A9: J1.117, U1.51 (A9)
/A10: J1.114, U1.48 (A10)
/A11: J1.113, U1.47 (A11)
/A12: J1.112, U1.46 (A12)
/A13: J1.111, U1.45 (A13)
/A14: J1.108, U1.43 (A14)
/A15: J1.107, U1.42 (A15)
/A16: J1.106, U1.41 (A16)
/A17: J1.105, U1.40 (A17)
/A18: J1.102, U1.39 (A18)
/A19: J1.101, U1.38 (A19)
/A20: J1.100, U1.37 (A20)
/A21: J1.99, U1.36 (A21)
/A22: J1.96, U1.34 (A22)
/A23: J1.95, U1.33 (A23)
/A24: J1.94, U1.32 (A24)
/A25: J1.93, U1.31 (A25)
/A26: J1.90, U1.29 (A26)
/A27: J1.89, U1.28 (A27)
/A28: J1.88, U1.27 (A28)
/A29: J1.87, U1.26 (A29)
/A30: J1.84, U1.24 (A30)
/A31: J1.83, U1.23 (A31)
/CLK: J1.34, U1.6 (CLK)
/D0: J1.152, U1.75 (D0)
/D1: J1.151, U1.76 (D1)
/D2: J1.154, U1.78 (D2)
/D3: J1.153, U1.79 (D3)
/D4: J1.158, U1.80 (D4)
/D5: J1.157, U1.81 (D5)
/D6: J1.160, U1.82 (D6)
/D7: J1.159, U1.83 (D7)
/D8: J1.164, U1.86 (D8)
/D9: J1.163, U1.87 (D9)
/D10: J1.166, U1.88 (D10)
/D11: J1.165, U1.89 (D11)
/D12: J1.170, U1.91 (D12)
/D13: J1.169, U1.92 (D13)
/D14: J1.172, U1.93 (D14)
/D15: J1.171, U1.94 (D15)
/D16: J1.176, U1.96 (D16)
/D17: J1.175, U1.97 (D17)
/D18: J1.178, U1.98 (D18)
/D19: J1.177, U1.99 (D19)
/D20: J1.182, U1.101 (D20)
/D21: J1.181, U1.102 (D21)
/D22: J1.184, U1.103 (D22)
/D23: J1.183, U1.104 (D23)
/D24: J1.188, U1.106 (D24)
/D25: J1.187, U1.107 (D25)
/D26: J1.190, U1.108 (D26)
/D27: J1.189, U1.109 (D27)
/D28: J1.194, U1.111 (D28)
/D29: J1.193, U1.112 (D29)
/D30: J1.196, U1.113 (D30)
/D31: J1.195, U1.114 (D31)
/FC0: J1.42, U1.12 (FC0)
/FC1: J1.41, U1.10 (FC1)
/FC2: J1.38, U1.9 (FC2)
/R~W~: J1.5, U1.117 (R~W~)
/SIZ0: J1.10, U1.120 (SIZ0)
/SIZ1: J1.9, U1.119 (SIZ1)
/~AS~: J1.18, U1.125 (~AS~)
/~AVEC~: J1.37, U1.7 (~AVEC~)
/~BERR~: J1.26, U1.130 (~BERR~)
/~BGACK~: J1.53, U1.17 (~BGACK~)
/~BG~: J1.50, U1.16 (~BG~)
/~BR~: J1.54, U1.20 (~BR~)
/~CBACK~: J1.22, U1.127 (~CBACK~)
/~CBREQ~: J1.21, U1.126 (~CBREQ~)
/~CDIS~: J1.140, U1.71 (~CDIS~)
/~CIIN~: J1.14, U1.122 (~CIIN~)
/~CIOUT~: J1.49, U1.15 (~CIOUT~)
/~DBEN~: J1.13, U1.121 (~DBEN~)
/~DSACK~0: J1.33, U1.3 (~DSACK~0)
/~DSACK~1: J1.30, U1.132 (~DSACK~1)
/~DS~: J1.17, U1.124 (~DS~)
/~ECS~: J1.6, U1.118 (~ECS~)
/~HALT~: J1.25, U1.129 (~HALT~)
/~IPEND: J1.129, U1.62 (~IPEND~)
/~IPL~0: J1.139, U1.70 (~IPL~0)
/~IPL~1: J1.136, U1.69 (~IPL~1)
/~IPL~2: J1.134, U1.68 (~IPL~2)
/~MMUDIS~: J1.133, U1.65 (~MMUDIS~)
/~OCS~: J1.46, U1.14 (~OCS~)
/~REFILL~: J1.143, U1.73 (~REFILL~)
/~RESET~: J1.130, U1.64 (~RESET~)
/~RMC~: J1.45, U1.13 (~RMC~)
/~STATUS~: J1.145, U1.74 (~STATUS~)
/~STERM~: J1.29, U1.131 (~STERM~)
GND: H1.1, H2.1, H3.1, H4.1, J1.1, J1.2, J1.7, J1.8, J1.15, J1.16, J1.23, J1.24, J1.31, J1.32, J1.39, J1.40, J1.47, J1.48, J1.55, J1.56, J1.63, J1.64, J1.71, J1.72, J1.73, J1.74, J1.77, J1.78, J1.85, J1.86, J1.97, J1.98, J1.109, J1.110, J1.121, J1.122, J1.131, J1.132, J1.141, J1.142, J1.147, J1.148, J1.155, J1.156, J1.167, J1.168, J1.179, J1.180, J1.191, J1.192, J1.199, J1.200, J1.203, J1.204, U1.1 (GND), U1.2 (GND), U1.5 (GND), U1.11 (GND), U1.19 (GND), U1.25 (GND), U1.35 (GND), U1.44 (GND), U1.57 (GND), U1.60 (GND), U1.66 (GND), U1.67 (GND), U1.77 (GND), U1.90 (GND), U1.95 (GND), U1.100 (GND), U1.110 (GND), U1.123 (GND)
VCC: J1.3, J1.4, J1.11, J1.12, J1.19, J1.20, J1.27, J1.28, J1.35, J1.36, J1.43, J1.44, J1.51, J1.52, J1.59, J1.60, J1.67, J1.68, J1.75, J1.76, J1.79, J1.80, J1.91, J1.92, J1.103, J1.104, J1.115, J1.116, J1.127, J1.128, J1.137, J1.138, J1.149, J1.150, J1.161, J1.162, J1.173, J1.174, J1.185, J1.186, J1.197, J1.198, J1.201, J1.202

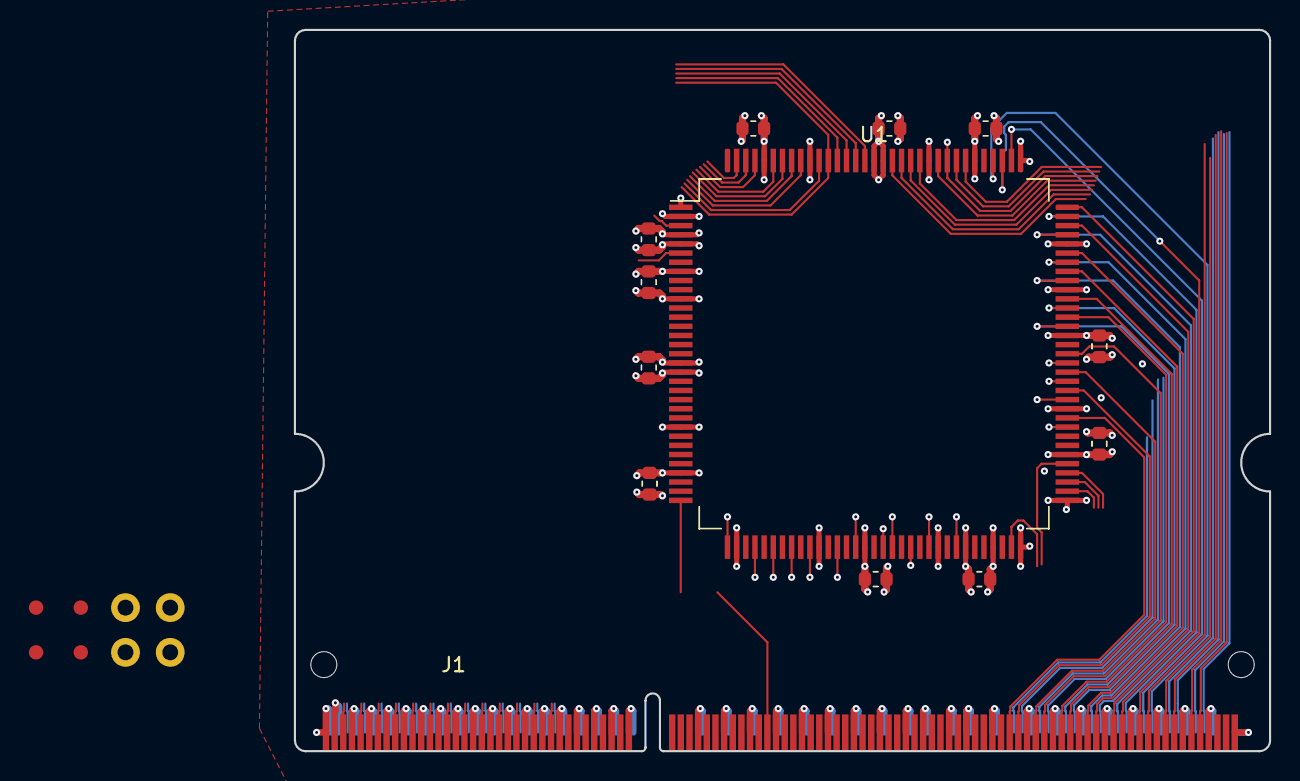
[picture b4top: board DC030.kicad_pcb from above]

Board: 4 copper layers, 67.6 x 50.0 mm, 10 parts (0 on the bottom side), 102 nets.

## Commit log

2021-09-15 Much progress
2021-09-15 add CPLD stuff
2021-09-15 Start getting it to work in Xilinx ISE
2021-09-15 more
2021-09-26 Documentation
2021-10-03 Draft of final verilog
2021-10-03 Can we compile it?
2021-10-03 Compiled but does it do anything?
2021-10-03 Compiles
2021-10-03 better
2021-10-04 Refactor a bit
2021-10-04 Implemeneted on LC4128ZE, LC4256C, and XC95144XL
2021-10-04 XC95144XL redo
2021-10-04 Remove FCS from FSB BERR
2021-10-05 fixed some stuff
2021-10-05 Switch to SRAM
2021-10-05 fake pinout applied to LC4064ZE
2021-10-07 Fix metastability issue going into refresh
2021-10-26 Lots
2021-10-27 STERMINATOR (sucks)
2021-10-27 Add LC... sloppy
2021-10-27 GS timing
2021-10-27 better sterminator for LC
